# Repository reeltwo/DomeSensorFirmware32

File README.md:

# Dome Sensor Ring Firmware

This is the sketch for the dome sensor ring board.

## Libraries Used

<ul>
<li>https://github.com/reeltwo/Reeltwo</li>
</ul>

## Serial Configuration commands

`#DPZERO`:
Factory reset all settings in EEPROM
*Examples*:

    #DPZERO

`#DPCONFIG`:
List all settings in EEPROM
*Examples*:

    #DPCONFIG

`#DPBAUD`[number]:
Specify sensor ring baud rate (default 57600)
*Examples*:

    #DPBAUD57600 (set baud rate to 57600)

`#DPMIN`[number]:
Specify sensor ring minimum analog reference value (default 0)
*Examples*:

    #DPMIN0 (set minimum analog reference to 0)

`#DPMAX`[number]:
Specify sensor ring maximum analog reference value (default 1023)
*Examples*:

    #DPMAX1023 (set maximum analog reference to 1023)

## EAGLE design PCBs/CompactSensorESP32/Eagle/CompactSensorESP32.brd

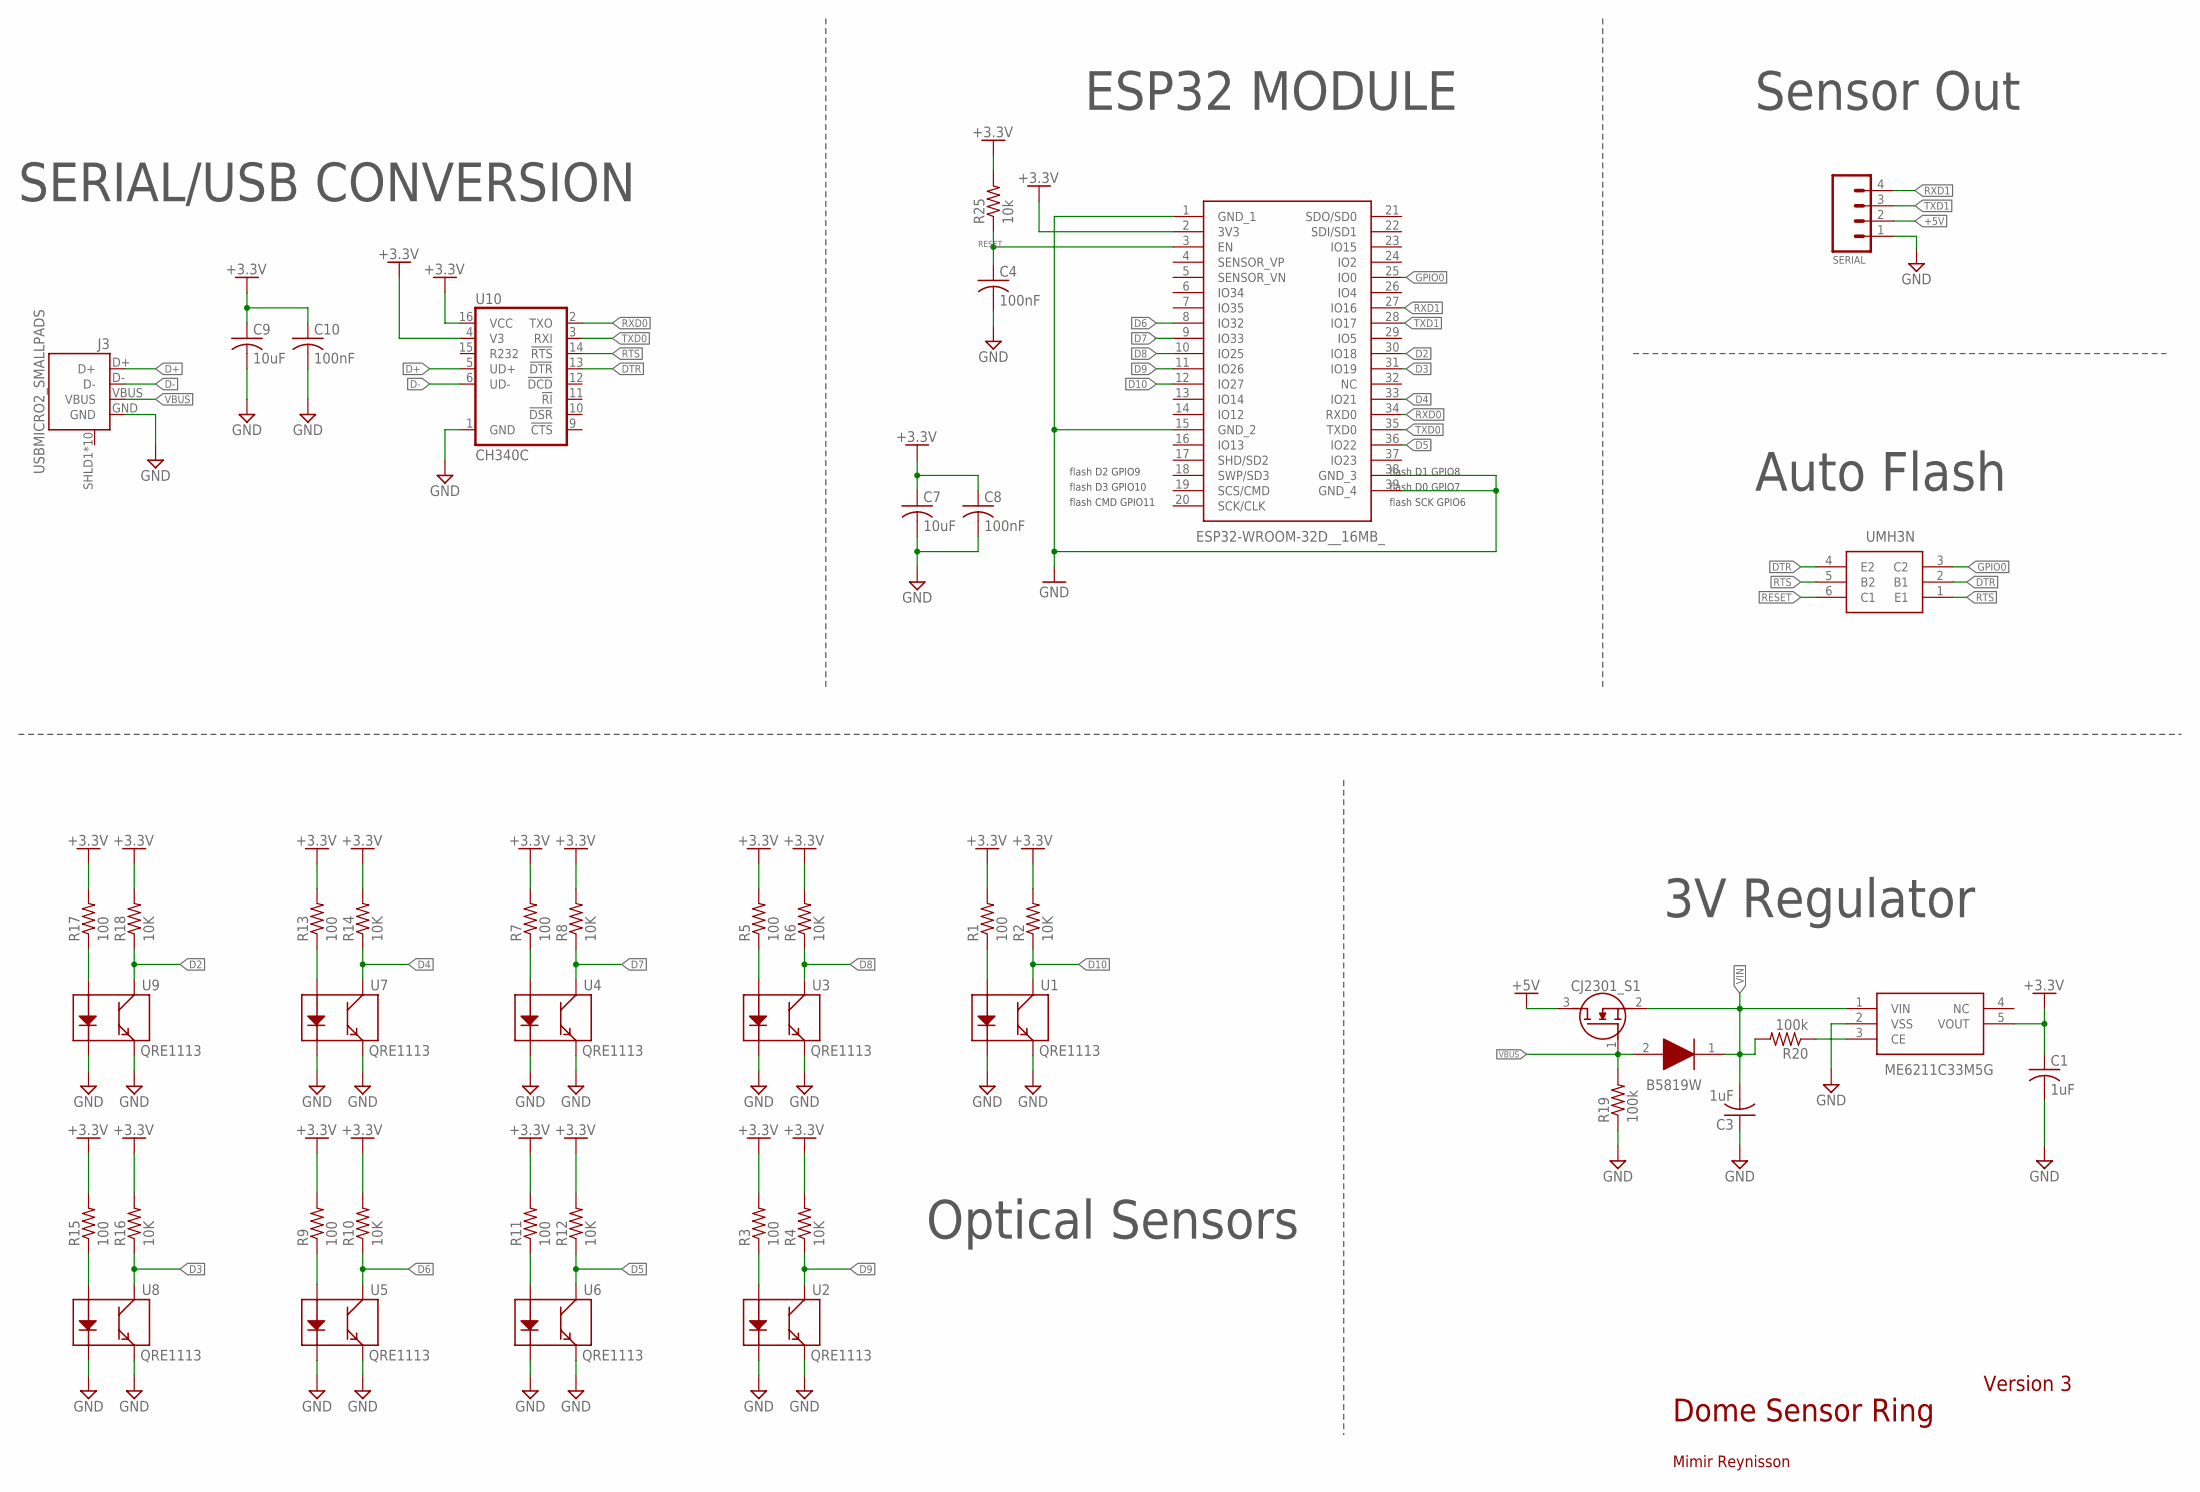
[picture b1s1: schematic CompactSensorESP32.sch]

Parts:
C1, C3: 1uF; SMD-0402
C4, C8, C10: 100nF; SMD-0402
C7, C9: 10uF; SMD-0402
D1: B5819W; SOD3716X125N
IC1: ESP32-WROOM-32D__16MB_; ESP32WROOM32D16MB
IC2: ME6211C33M5G; SOT95P282X145-5N
J3: USBMICRO2_SMALLPADS; USB-MICROB-10118194_SMALLPADS
Q1: UMH3N; SOT65P230X110-6N
Q2: CJ2301_S1; SOT95P240X115-3N
R1, R3, R5, R7, R9, R11, R13, R15, R17: 100; 0402-RES
R2, R4, R6, R8, R10, R12, R14, R16, R18: 10K; 0402-RES
R19, R20: 100k; SMD-0402
R25: 10k; SMD-0402
SERIAL: CONN_04POLAR; MOLEX-1X4
U1, U2, U3, U4, U5, U6, U7, U8, U9: QRE1113
U10: CH340C; SO016

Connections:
+3.3V: C1.1, C7.1, C8.1, C9.1, C10.1, IC1.2 (3V3), IC2.5 (VOUT), R1.2, R2.2, R3.2, R4.2, R5.2, R6.2, R7.2, R8.2, R9.2, R10.2, R11.2, R12.2, R13.2, R14.2, R15.2, R16.2, R17.2, R18.2, R25.2, U10.4 (V3), U10.16 (VCC)
+5V: Q2.3 (D), SERIAL.2
D2: IC1.30 (IO18), R18.1, U9.3 (C)
D3: IC1.31 (IO19), R16.1, U8.3 (C)
D4: IC1.33 (IO21), R14.1, U7.3 (C)
D5: IC1.36 (IO22), R12.1, U6.3 (C)
D6: IC1.8 (IO32), R10.1, U5.3 (C)
D7: IC1.9 (IO33), R8.1, U4.3 (C)
D8: IC1.10 (IO25), R6.1, U3.3 (C)
D9: IC1.11 (IO26), R4.1, U2.3 (C)
D10: IC1.12 (IO27), R2.1, U1.3 (C)
D+: J3.D+, U10.5 (UD+)
D-: J3.D-, U10.6 (UD-)
DTR: Q1.2 (B1), Q1.4 (E2), U10.13 (!DTR)
GND: C1.2, C3.1, C4.2, C7.2, C8.2, C9.2, C10.2, IC1.1 (GND_1), IC1.15 (GND_2), IC1.38 (GND_3), IC1.39 (GND_4), IC2.2 (VSS), J3.GND, R19.1, SERIAL.1, U1.2 (K), U1.4 (E), U2.2 (K), U2.4 (E), U3.2 (K), U3.4 (E), U4.2 (K), U4.4 (E), U5.2 (K), U5.4 (E), U6.2 (K), U6.4 (E), U7.2 (K), U7.4 (E), U8.2 (K), U8.4 (E), U9.2 (K), U9.4 (E), U10.1 (GND)
GPIO0: IC1.25 (IO0), Q1.3 (C2)
unnamed: R1.1, U1.1 (A)
unnamed: R3.1, U2.1 (A)
unnamed: R5.1, U3.1 (A)
unnamed: R7.1, U4.1 (A)
unnamed: R9.1, U5.1 (A)
unnamed: R11.1, U6.1 (A)
unnamed: R13.1, U7.1 (A)
unnamed: R15.1, U8.1 (A)
unnamed: R17.1, U9.1 (A)
unnamed: IC2.3 (CE), R20.1
RESET: C4.1, IC1.3 (EN), Q1.6 (C1), R25.1
RTS: Q1.1 (E1), Q1.5 (B2), U10.14 (!RTS)
RXD0: IC1.34 (RXD0), U10.2 (TXO)
RXD1: IC1.27 (IO16), SERIAL.4
TXD0: IC1.35 (TXD0), U10.3 (RXI)
TXD1: IC1.28 (IO17), SERIAL.3
VBUS: D1.2 (A), J3.VBUS, Q2.1 (G), R19.2
VIN: C3.2, D1.1 (K), IC2.1 (VIN), Q2.2 (S), R20.2

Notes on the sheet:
Optical Sensors
ESP32 MODULE
SERIAL/USB CONVERSION
flash D2 GPIO9
flash D3 GPIO10
flash CMD GPIO11
flash SCK GPIO6
flash D0 GPIO7
flash D1 GPIO8
3V Regulator
Auto Flash
Dome Sensor Ring
Sensor Out
Version 3
Mimir Reynisson

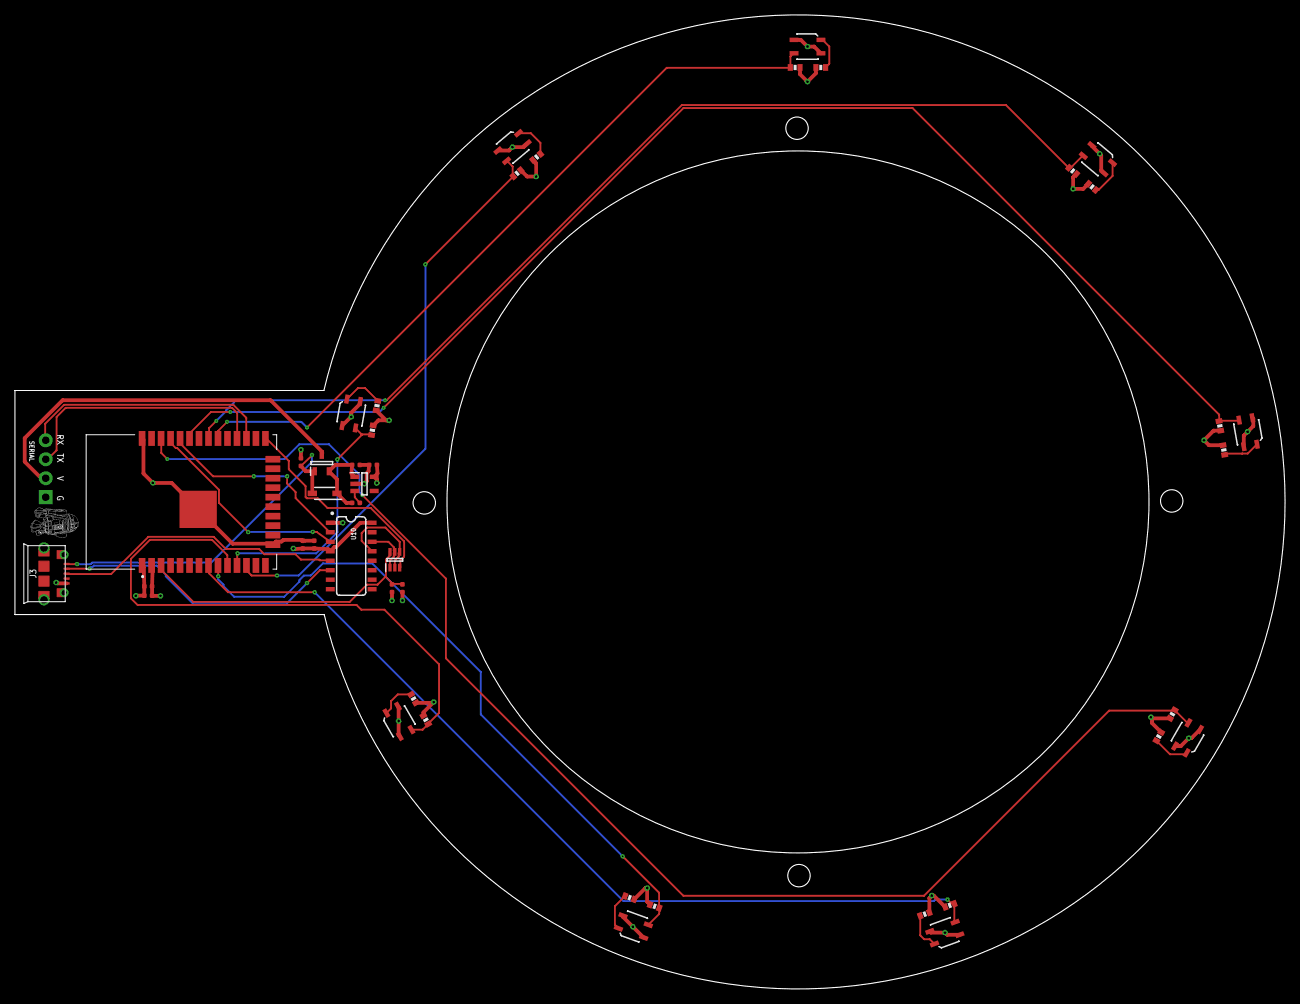
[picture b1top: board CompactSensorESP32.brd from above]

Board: 4 copper layers, 170.0 x 130.4 mm, 45 parts (0 on the bottom side), 34 nets.

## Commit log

2022-08-10 Added automation marker
2022-09-11 Disable USE_DEBUG
2022-09-11 Updated gitignore
2022-09-30 Changed default baudrate to 115200. Baudrate is settible by using #DPBAUD. Added #DPVERBOSE so sensor will print out current position on USB serial for debugging. Added error reporting when receiving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
2022-10-01 Changed default baud rate to 115200
2022-10-03 Fixed missing line ending
2023-05-20 Initial release
2023-06-06 Updated Makefile and added CompactSensorESP32 PCB files
2023-06-06 Added DomeSensorCompact pattern SVG file

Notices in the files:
parts and their libraries:
SparkFun-IC-Comms: Licensing: Creative Commons ShareAlike 4.0 International - https://creativecommons.org/licenses/by-sa/4.0
